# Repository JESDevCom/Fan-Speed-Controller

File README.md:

# Fan-Speed-Controller

**Part I. Introduction**
   * Re-Engineering a YLFC700 Fan Speed Controller (TRIAC based). This controller was originally sourced from an Xtrodinair Apex 42 Fireplace. The problem with the controller is that the slide potentiometer fails over time (about every 2-years). It fails at the slider's position where the fan runs just below max speed. 

**Part II. Theory for Failure**
   * The potentiometer is rated for 100[mW].
   * The reason the potentiometer fails is because the 47 [nF] Film capacitor begins to fail from transient voltage spikes after many startups.
   
**Part III. Testing Equipment Used**
1. Fluke 87V Digital Multimeter
2. Siglent SDS 1104X-E 100MHz Oscilloscope
3. Krohn-Hite Model 1600 3MHz Frequency Generator
4. Generic 5[V] 1[A] Fixed Power Supply
5. Hakko Soldering Station
6. Quick Hot Air Soldering Station

**Part IV. Software Used**
1. Windows 10 Pro
2. KiCAD 5.1
3. Matlab

**Part V. Parts Used**
1. RV1, 91A1A-B28-A22L, 0.2 [Ohms] to 250 [kOhms] Linear Potentiometer, Turn Knob Style, 2[W] max.
2. R1, 2.4k, Reused
3. R2, 270k, (Min: 0.25[W], Bought: 0.5[W])
4. R3, 18k,  (Min: 0.25[W], Bought: 0.5[W])
5. R4, 240k, (Min: 0.25[W], Bought: 0.5[W])
6. R5, 24, (Bought: 1[W])
7. U1, BTA16-600B, TRIAC (non-insulated tab package)
8. U2, DB3, DIAC (15 [uA] breakover current is my guess).
9. C3, 100 [nF], Film Capacitor 250[Vdc]
10. C2, 100[nF], Film Capacitor 250[Vdc]
11. C1, 47[nF], Ceramic Capacitor 1 [kVdc] (X7R)
12. L1, Inductor 7[uH] @ 1[KHz] (Measured with Scope, see characterization plot in Matlab folder)
13. 1/4" Dia. Metal Knob for Potentiometer

**Part VI. LTspice Simulation**
   * As the 47 [nF] fails, the potentiometer begins to seriously fall out of spec. 
   * Note, that the Power Factor (PF) is approximately 86% in the potentiometer resistance range where the slider fails (100 to 30k).

**Part VII. KiCAD Schematic**
   * Since this Controller adjusts the blower's speed on the fireplace and this motor is rated for 1.8 [A], let's design the PCB for double the max operating current because we can :). 
   * The only added components from the original design:
      1. 4 [A] fuse will be added, 
      2. a 24 [Ohm] resistor will be added in series with the potentionmeter since the potentiometer's minimum resistance is 0.2 [Ohms],
      3. a toggle switch to disconnect the controller from the 120 Volt mains to recreated the off detent that was on the original board, 
      4. and my design will not have any exposed PCB traces from the Fab.
      
   * We will reuse:
      1. 2.4k through-hole resistor,
      2. the two 100 [nF] film capacitors, 
      3. TRIAC, 
      4. DIAC, 
      5. and Inductor since these reactive components were engineered for use in the original design.

   * We will replace:
      1. 18k through-hole with a 18k in a 1206 package,
      2. 240k through-hole with a 240k in a 1206 package,
      3. 270k through-hole with a 270k in a 1206 package,
      4. the no-name slide potentiometer with a Bourns 91A1A-B28-A22L Knob Potentiometer,
      5. 47 [nF] 400 [Vdc] Radial Film Capacitor with a 47 [nF] 1 [kVdc] (X7R) Radial Ceramic Capacitor
     
   * A Bourns 91A1A-B28-A22L Knob Potentiometer (2[W], 0.2 to 250k [Ohms], linear) will repalce the original slide potentiometer (100[mW], 30 to 300k [Ohms], log). Since this potentiometer is in parallel with two other resistors, a 240k and 296k [ohms], the max resistance of the potentiometer doesn't matter that much. However, the minimum reistance does matter because it greatly affects the max speed (ie, the potentiometer controls the rate that the capacitors charge, which controls how the 120 [Vac] sinewave is chopped; thereby, changing the fan speed. marvelous).
   * Since the potentiometer goes down to 0.2 [Ohms], an excessive amount of current is drawn across the potentiometer, so a 24 Ohm resistor will be added in series with the potentiometer to approximately match the original slide potentiometer's minimum resistance. 
  
 **Part VIII. KiCAD PCB Design**
   * A two-side PCB will be created and fabricated, I used OSHpark as the frabricator.
   * SMD resistors for the 18k, 240k, 270k, 24 Ohm Resistors are required to make space for the Knob Potentiometer.
   * Certain traces that follow from the VAC input, to the TRIAC, and out to the motor must be fat traces (4mm) to stay below current and heat limits of having covered traces.
   * 0.2mm minimum distance between traces is important for 120[Vac] designs.

**Part IX. Disassembly of Original Boar & Removal of Components**
   * Remove the plastic & copper PCB mounting stands that connect the PCB to the metal outlet mount.
   * Use a Soldering Iron or Hot Air Station to remove the inductor, DIAC, TRIAC, and Capacitors.
   * Check capacitors with Fluke 87V.
   * Resolder the new and old components to the new board. 

**Part X. Results**
   * When removing the capacitors from the original board, the 47 [nF] Film Capacitor was measured at 1.2 [nF]. The 100 [nF] film capacitors were still in 10% spec.
   * After simulating the LTspice model with such a value (1.0nF) it became clear that the reason the potentiometer failed was because the 47 [nF] capacitor failed. This 47 [nF] capacitor is marked C1 on the original board (YLFC700).
   * Reason for failure: the capacitor is configured as a snubber and there is likely overvoltage spikes due to the motor.
   * Solution: Use a cermaic capacitor that has a higher maximum voltage rating that can withstand spikes resulting from the TRIAC switching. 
   
   * Successfully operating as of March 2021.

**Part XI. Legal Notice**
 
Under the MIT license to this project, you may use this design freely. An email to alledgedlyengineering @ gmail stating that you used this design would be nice to know. By using this project you are agreeing to the risks involved with AC current and altering a UL listed product to fit your needs. In addition, you agree to not hold me responsible for any injury or result of injury incurred by modifying the YLFC700 Fan Speed Controller. This project has no affliations with any of the manufacturers used in this design or the PCB fabrication house used.

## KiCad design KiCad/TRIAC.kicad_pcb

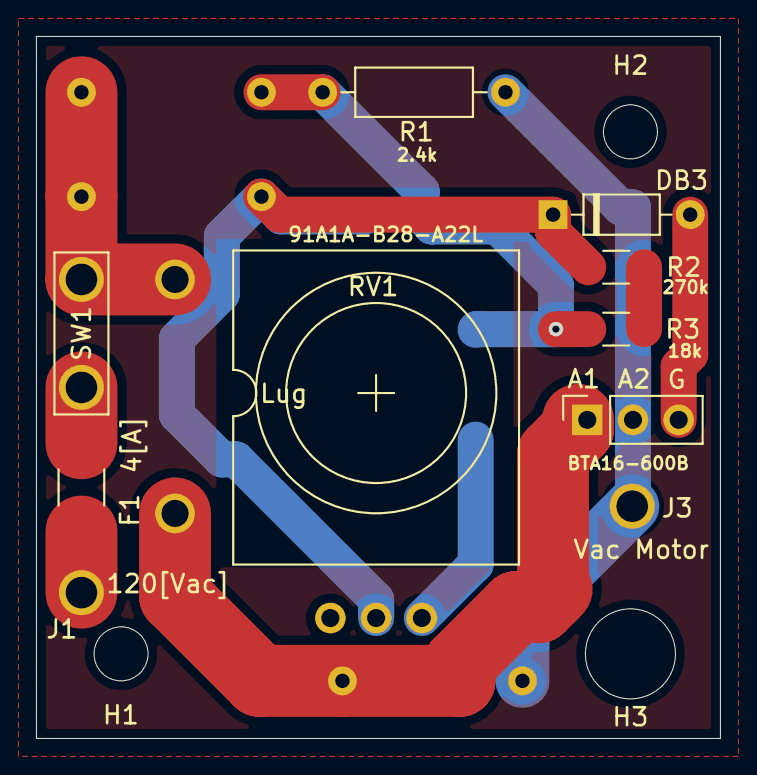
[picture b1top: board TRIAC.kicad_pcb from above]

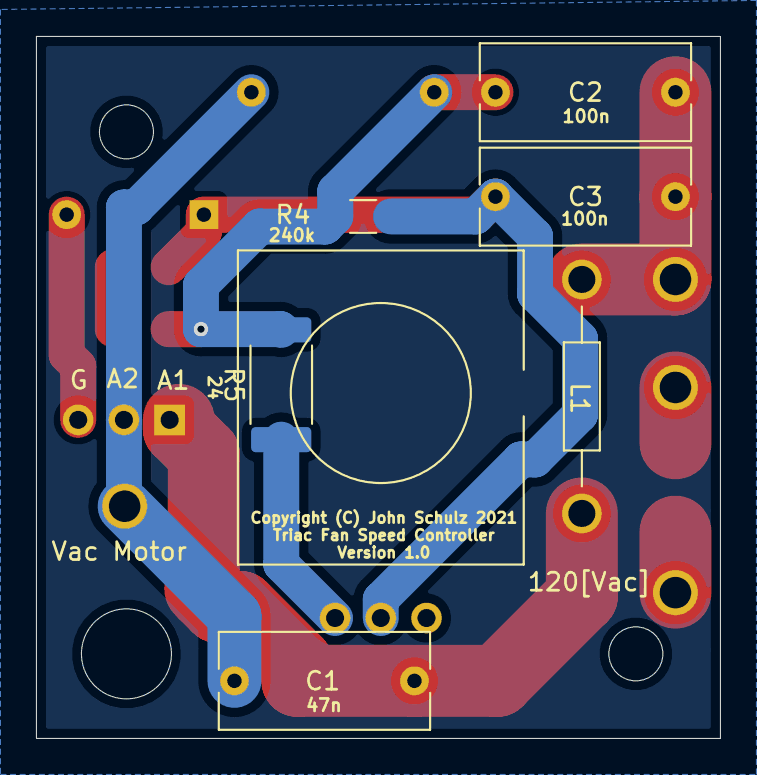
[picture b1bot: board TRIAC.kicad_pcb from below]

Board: 2 copper layers, 38.0 x 39.0 mm, 19 parts (6 on the bottom side), 10 nets.

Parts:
C1: 47n; C_Rect_L11.5mm_W5.2mm_P10.00mm_MKT
C2, C3: 100n; C_Rect_L11.5mm_W5.2mm_P10.00mm_MKT
D1: DB3; D_DO-35_SOD27_P7.62mm_Horizontal
F1: Fuse; FUSC6125X279N
H1, H2: MountingHole; MountingHole_3mm
H3: MountingHole; MountingHole_5mm
J1: BlackWire; Pin_D1.7mm
J3: WhiteWire; Pin_D1.7mm
L1: L_Core_Ferrite; TRIAC_Choke
Q1: BTA16-600B; PinSocket_1x03_P2.54mm_Vertical
R1: 2.4k; R_Axial_DIN0207_L6.3mm_D2.5mm_P10.16mm_Horizontal
R2: 270k; R_1206_3216Metric_Pad1.30x1.75mm_HandSolder
R3: 18k; R_1206_3216Metric_Pad1.30x1.75mm_HandSolder
R4: 240k; R_1206_3216Metric_Pad1.30x1.75mm_HandSolder
R5: 24; R_2512_6332Metric_Pad1.40x3.35mm_HandSolder
RV1: R_POT_10_to_300k; 91A1A-B28-A22L-Bottom
SW1: SW_DIP_x01; GRS-2011-2055

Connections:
unnamed: C1.1, L1.2, Q1.1
unnamed: C1.2, J3.1, Q1.2, R1.2
unnamed: C2.1, C3.1, L1.1, SW1.2
unnamed: C2.2, R1.1, R3.2, R4.2, R5.2
unnamed: C3.2, D1.1, R2.1, R4.1, RV1.2
unnamed: D1.2, Q1.3
unnamed: F1.1, SW1.1
unnamed: F1.2, J1.1
unnamed: R2.2, R3.1
unnamed: R5.1, RV1.3

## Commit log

2021-02-15 Project Files
2021-03-01 Updating Results and C1 Part change
2021-03-01 Spelling Corrections
2021-03-26 spelling error
2021-03-26 bolding and title numbering

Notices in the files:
KiCad/TRIAC.kicad_pcb:
Copyright (C) John Schulz 2021
